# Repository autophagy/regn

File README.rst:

.. image:: seonu/_static/github_header.png
    :align: center

Regn is a weather station. It reads in temperature humidity,
atmospheric pressure and luminosity.

Hardware
========

- `ESP8266 Huzzah`_
- `DHT22 temperature & humidity sensor`_
- `BMP180 barometric pressure sensor`_
- `TSL2561 luminosity/lux/light sensor`_

Schematic
---------

.. image:: seonu/_static/schema.png

PCB
---

.. image:: seonu/_static/board.png

Front
~~~~~

.. image:: seonu/_static/pcb_front.png

Back
~~~~

.. image:: seonu/_static/pcb_back.png

Software
========

Interface
---------

.. image:: seonu/_static/interface.png

.. _ESP8266 Huzzah: https://cdn-learn.adafruit.com/downloads/pdf/adafruit-huzzah-esp8266-breakout.pdf
.. _DHT22 temperature & humidity sensor: https://www.sparkfun.com/datasheets/Sensors/Temperature/DHT22.pdf
.. _BMP180 barometric pressure sensor: https://cdn-shop.adafruit.com/datasheets/BST-BMP180-DS000-09.pdf
.. _TSL2561 luminosity/lux/light sensor: https://cdn-shop.adafruit.com/datasheets/TSL2561.pdf

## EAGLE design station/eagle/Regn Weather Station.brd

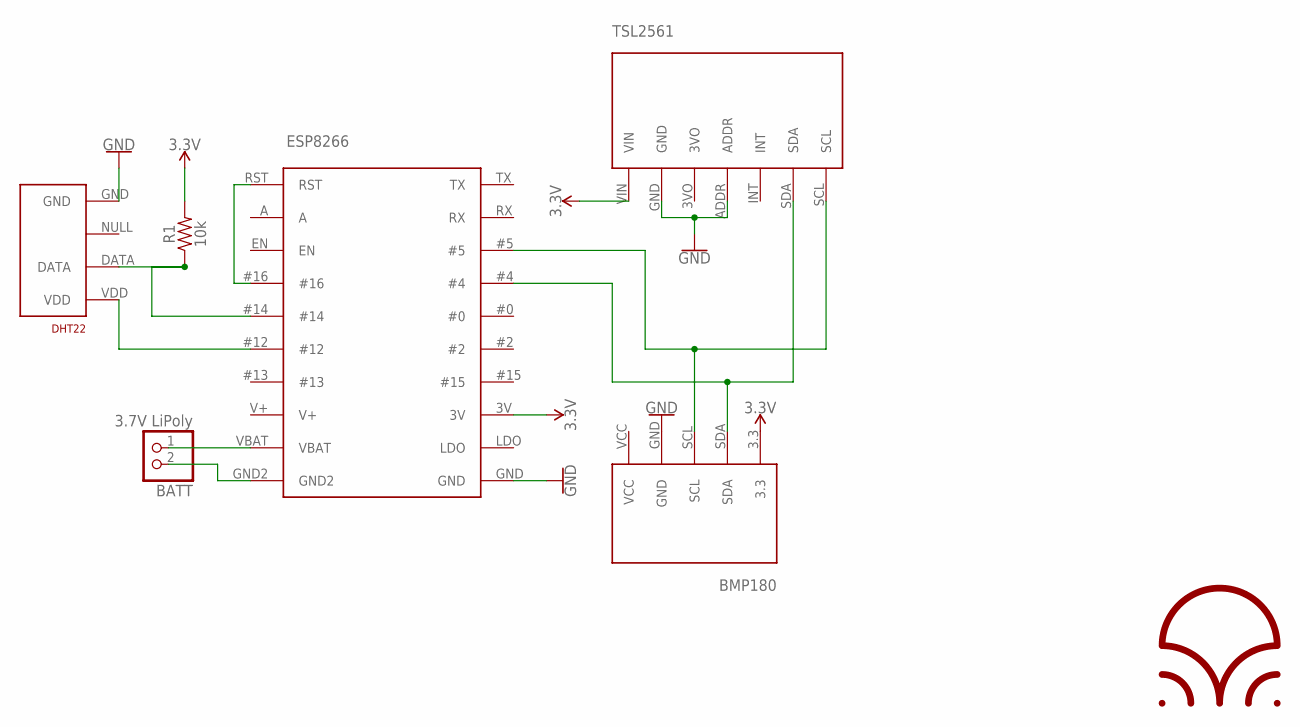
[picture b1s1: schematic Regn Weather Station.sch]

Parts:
BATT: 3.7V LiPoly; JST-PH-2-SMT
BMP180: BMP180
DHT22: RHT03_DHT-22_AM2302WIRED; AM2302
ESP8266: ESP8266HUZZAH
R1: 10k; AXIAL-0.3
TSL2561: TSL2561

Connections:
3.3V: BMP180.3.3, ESP8266.3V, R1.P$2 (2), TSL2561.VIN
GND: BMP180.GND, DHT22.GND, ESP8266.GND, TSL2561.ADDR, TSL2561.GND
unnamed: DHT22.DATA, ESP8266.#14, R1.P$1 (1)
unnamed: DHT22.VDD, ESP8266.#12
unnamed: BMP180.SDA, ESP8266.#4, TSL2561.SDA
unnamed: ESP8266.#16, ESP8266.RST
unnamed: BMP180.SCL, ESP8266.#5, TSL2561.SCL
unnamed: BATT.1 (2), ESP8266.VBAT
unnamed: BATT.2 (1), ESP8266.GND2
V+: ESP8266.V+
VCC: BMP180.VCC

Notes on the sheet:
/home/mika/images/regn.bmp

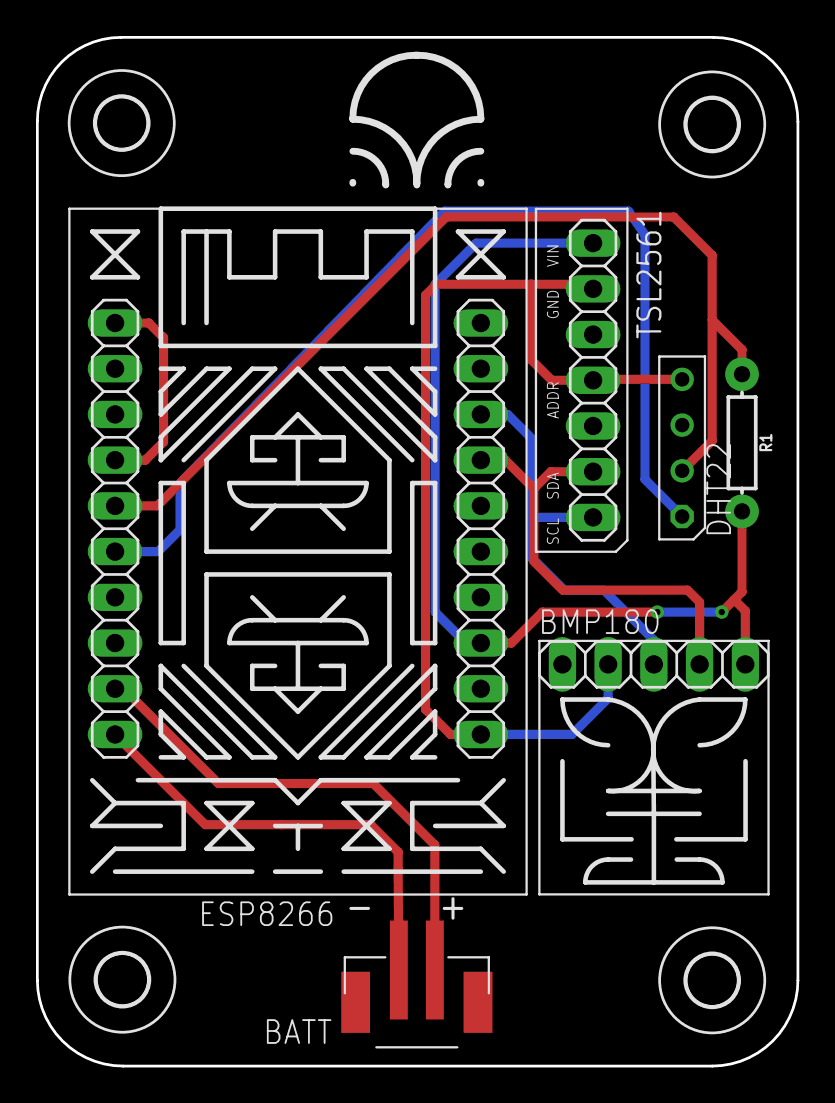
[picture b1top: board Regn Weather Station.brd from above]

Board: 2 copper layers, 42.3 x 57.1 mm, 10 parts (0 on the bottom side), 9 nets.

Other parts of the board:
U$1, U$2, U$3, U$4: 2,8

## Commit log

2018-04-01 Initial commit of schematics
2018-04-01 Add interface design
2018-04-01 Remove bluetooth module
2018-04-02 Add logo
2018-04-07 Convert station code from arduino to ESP8266
2018-04-07 Add connection and POST to defined endpoint
2018-04-07 Remove arduino refernces
2018-04-07 Update station schematics
2018-04-08 Add 10k pullup to DHT22 data pin
2018-04-08 gitignore
2018-04-08 Sketch out API structure
2018-04-08 Add sensor data insert json schema + validation
2018-04-08 Experimentation with db, add insert and latest
2018-04-08 Add sensor/range/since api
2018-04-09 Fix luminosity label on station
2018-04-09 Add timestamp to sensor get
2018-04-10 Add prototype dashboard that calls from API
2018-04-10 Add favicon
2018-04-10 Genericise js into a dashboard object
2018-04-10 Add mode and granularity switching to dashboard obj
2018-04-10 Expose coords through latest api endpoint
2018-04-10 Refresh latest every 10 seconds
2018-04-10 Add graph refresh
2018-04-11 Tweak x axis ticks
2018-04-12 Change graph distribution to linear
2018-04-12 Add min and max to graph depending on the granularity
2018-04-12 Reduce data down to 50 datapoints
2018-04-12 Move averaging of datapoints into server, expose via api
2018-04-12 Only reduce dataset if desired datapoints number is less than the dataset
2018-04-14 Add sensor type controls
2018-04-14 Add granularity controls
2018-04-14 Add default value if latest results are not there
2018-04-14 Add 'NO DATA' message
2018-04-14 Fix graph shrinking
2018-04-15 Add configuration based on FLASK_CONFIG
2018-04-15 Add API key check for insert endpoint
2018-04-15 Restructured flask project
2018-04-15 Refactor sample data generator to use development api key
2018-04-15 Procfile
2018-04-15 Fix a few bugs, get gunicorn to work properly
2018-04-16 Reorder sensor controls
2018-04-16 Add check for zero values from sensors
2018-04-17 POST to regn (on heroku) endpoint over https
2018-04-20 Updated station schematics to include 3.7v lipo, pin 16 -> RST for deepsleep, toggleable 3.3v rail for dht22
2018-04-21 Move diagrams from Fritzing to Eagle
    Also create prelim prototype PCB
2018-04-22 Refactored PCB size and logos
2018-04-22 Increased trace width 0.6 -> 1.0 mil
2018-04-23 Increased trace width from 10 mil to 20 mil
2018-04-23 Fix some clearance issues
2018-05-10 PCB optimizations and refining
2018-07-29 DHT22 on pin 14, powered by pin 12

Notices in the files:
parts and their libraries:
SparkFun-Resistors: Licensing: Creative Commons ShareAlike 4.0 International - https://creativecommons.org/licenses/by-sa/4.0
